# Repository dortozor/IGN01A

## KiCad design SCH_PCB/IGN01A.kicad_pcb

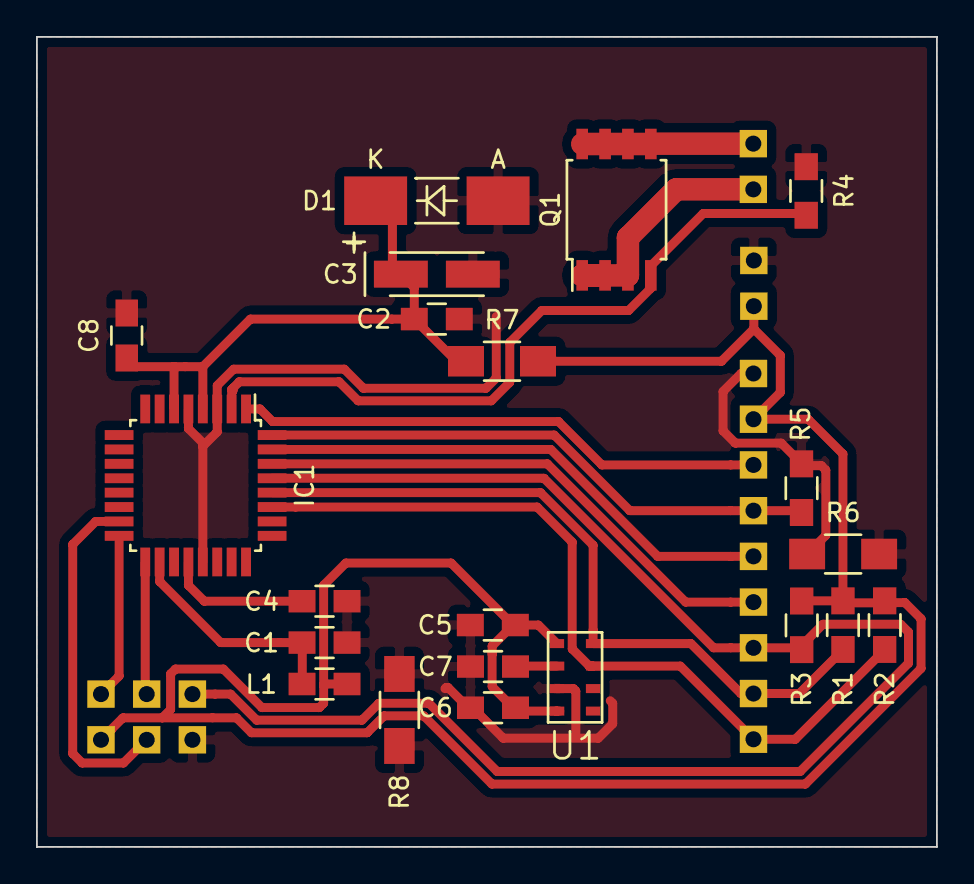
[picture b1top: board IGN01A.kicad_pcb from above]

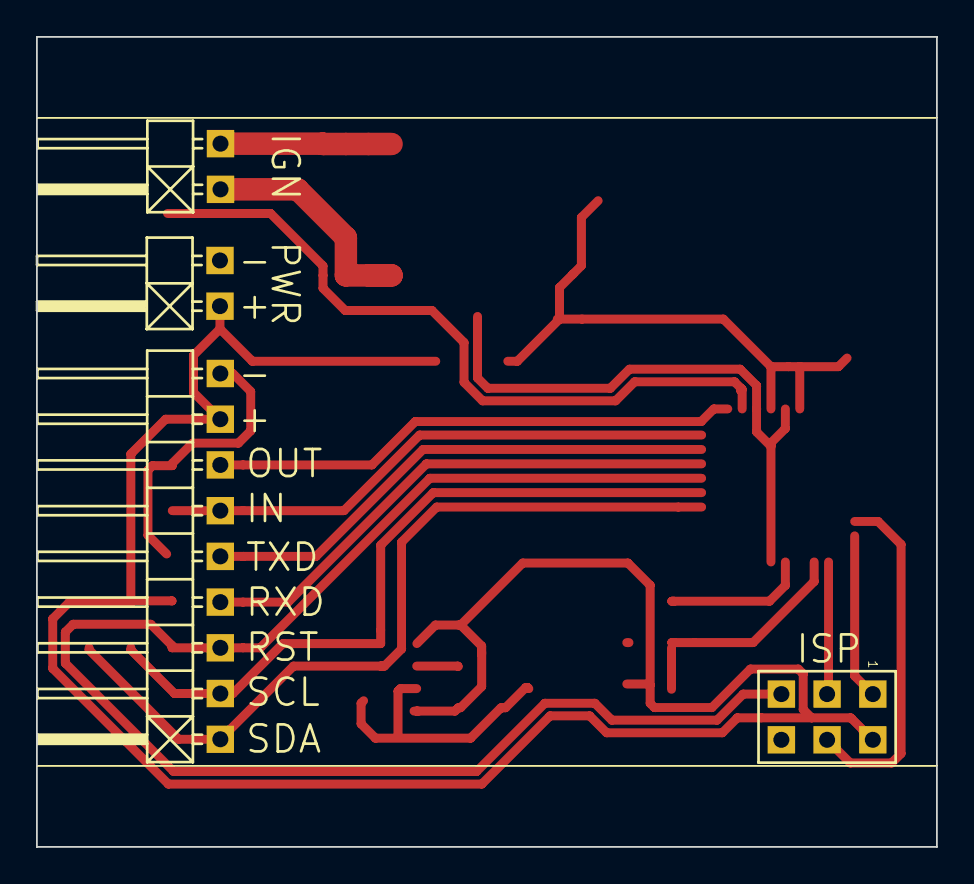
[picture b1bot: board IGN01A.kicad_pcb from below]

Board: 2 copper layers, 50.0 x 45.0 mm, 25 parts (4 on the bottom side), 18 nets.

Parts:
C1, C2, C4, C6, C7, C8: 100nF; C_0805_HandSoldering
C3: 22uF/6.3V; TantalC_SizeA_EIA-3216_HandSoldering
C5: 10uF; C_0805_HandSoldering
D1: 1N4007; Diode-MELF_Handsoldering
IC1: ATMEGA328-A; TQFP-32_7x7mm_Pitch0.8mm
J1: PWR; Angled_1x02
J2: IGN; Angled_1x02
J3: HEADER_1x09; Angled_1x09
J5: ISP; Straight_2x03
L1: 10uH; C_0805_HandSoldering
Q1: IRF7413ZPBF; SOIJ-8_5.3x5.3mm_Pitch1.27mm
R1, R2, R3, R4, R5: 10k; R_0805_HandSoldering
R6, R7, R8: 0; R_1206_HandSoldering
U1: MPL3115A2; LGA-MPL3115A

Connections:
/IGN: IC1.2, Q1.4, R4.1
/IN: IC1.32, J3.6, R5.1
/MISO: IC1.16, J5.1
/MOSI: IC1.15, J5.4
/OUT: IC1.1, J3.7
/RST: IC1.29, J3.3, J5.5, R3.2
/RXD: IC1.30, J3.4
/SCK: IC1.17, J5.3
/SCL: IC1.28, J3.2, R1.2, U1.8
/SDA: IC1.27, J3.1, R2.2, U1.7
/TXD: IC1.31, J3.5
GND: C1.2, C2.2, C3.2, C4.2, C5.2, C6.2, C7.2, C8.2, D1.2, IC1.3, IC1.5, IC1.21, J1.2, J3.9, J5.6, R4.2, R5.2, R6.1, R6.2, R8.1, R8.2, U1.3
unnamed: C4.1, IC1.20
unnamed: C7.1, U1.2
unnamed: J2.1, Q1.1, Q1.2, Q1.3
unnamed: J2.2, Q1.5, Q1.6, Q1.7, Q1.8
VAA: C1.1, IC1.18, L1.1
VDD: C2.1, C3.1, C5.1, C6.1, C8.1, D1.1, IC1.4, IC1.6, J1.1, J3.8, J5.2, L1.2, R1.1, R2.1, R3.1, R7.1, R7.2, U1.1, U1.4

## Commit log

2015-09-26 Inital commit
2015-09-27 Minor PCB tweaks
